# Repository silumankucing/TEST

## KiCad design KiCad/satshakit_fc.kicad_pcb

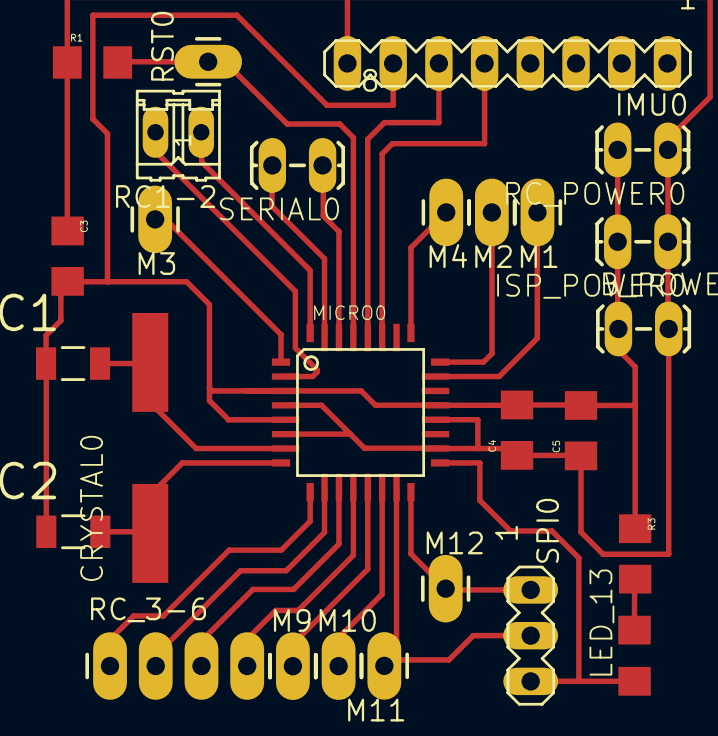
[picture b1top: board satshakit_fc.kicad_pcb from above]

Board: 2 copper layers, 27 parts (0 on the bottom side), 25 nets.

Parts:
B_POWER0: 1X02_LOCK_LONGPADS
C1, C2: 22pF; CAPC3216X178N
C3: 10uF; 1206
C4: 1uF; 1206
C5: 100nF; 1206
CRYSTAL0: 16Mhz; CSM-7X-DU
IMU0: MA08-1
ISP_POWER0: 1X02_LOCK_LONGPADS
LED_13: YELLOW; 1206
M1, M2, M3, M4, M9, M10, M11, M12: M01PTH_LONGPAD; 1X01_LONGPAD
MICRO0: ATMEGA328P-AU; TQFP32-08
R1: 10k; 1206
R3: 499; 1206
RC1-2: 02P
RC_3-6: 1X04_LONGPADS
RC_POWER0: 1X02_LOCK_LONGPADS
RST0: M01PTH_LONGPAD; 1X01_LONGPAD
SERIAL0: 1X02_LOCK_LONGPADS
SPI0: MA03-1

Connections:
GND_B: B_POWER0.1, C1.1, C2.1, C3.2, C4.2, C5.2, IMU0.7, ISP_POWER0.2, MICRO0.3, MICRO0.5, MICRO0.21, R3.1, RC_POWER0.2
M3: M3.1, MICRO0.1
M9: M9.1, MICRO0.13
M10: M10.1, MICRO0.14
MA0: M1.1, MICRO0.23
MA1: M2.1, MICRO0.24
MA2: M4.1, MICRO0.25
MISO: M12.1, MICRO0.16, SPI0.1
MOSI: M11.1, MICRO0.15, SPI0.2
unnamed: C1.2, CRYSTAL0.2, MICRO0.7
unnamed: MICRO0.29, R1.2, RST0.1
unnamed: C2.2, CRYSTAL0.1, MICRO0.8
unnamed: LED_13.2, R3.2
R1: MICRO0.32, RC1-2.1
R2: MICRO0.2, RC1-2.2
R3: MICRO0.9, RC_3-6.1
R4: MICRO0.10, RC_3-6.2
R5: MICRO0.11, RC_3-6.3
R6: MICRO0.12, RC_3-6.4
RX: MICRO0.30, SERIAL0.1
SCK: LED_13.1, MICRO0.17, SPI0.3
SCL: IMU0.6, MICRO0.28
SDA: IMU0.5, MICRO0.27
TX: MICRO0.31, SERIAL0.2
VCC_B: B_POWER0.2, C3.1, C4.1, C5.1, IMU0.8, ISP_POWER0.1, MICRO0.4, MICRO0.6, MICRO0.18, MICRO0.20, R1.1, RC_POWER0.1

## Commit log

2024-02-24 Create hehe
